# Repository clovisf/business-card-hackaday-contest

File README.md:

# business-card-hackaday-contest
 uC business card for Hackaday contest

 This is my try on an electronic business card for the 2024 Hackaday business card contest

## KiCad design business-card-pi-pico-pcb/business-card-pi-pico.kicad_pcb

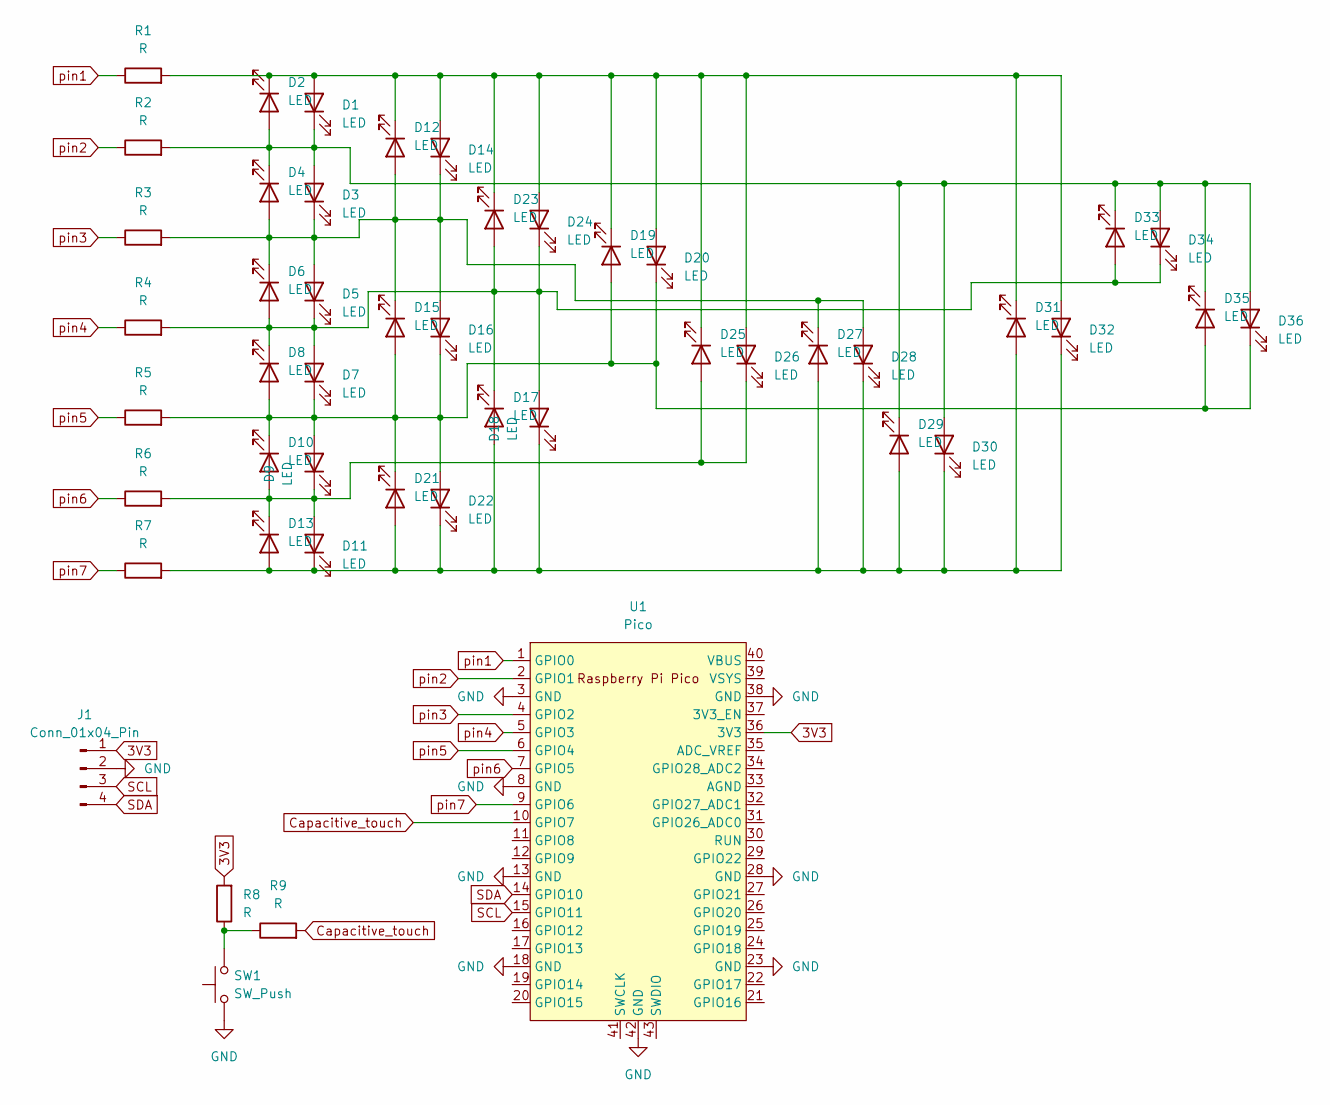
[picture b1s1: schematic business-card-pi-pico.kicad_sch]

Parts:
D1, D2, D3, D4, D5, D6, D7, D8, D9, D10, D11, D12, D13, D14, D15, D16, D17, D18, D19, D20, D21, D22, D23, D24, D25, D26, D27, D28, D29, D30, D31, D32, D33, D34, D35, D36: LED; LED_0805_2012Metric
J1: Conn_01x04_Pin; 128x64OLED
R1, R2, R3, R4, R5, R6, R7, R8, R9: R; R_0805_2012Metric
SW1: SW_Push; SW_PUSH_6mm_H8mm
U1: Pico; RPi_Pico_SMD_TH

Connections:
3V3: J1.1, R8.2, U1.36 (3V3)
Capacitive_touch: R9.2, U1.10 (GPIO7)
GND: J1.2, SW1.1, U1.3 (GND), U1.8 (GND), U1.13 (GND), U1.18 (GND), U1.23 (GND), U1.28 (GND), U1.38 (GND), U1.42 (GND)
unnamed: D1.2 (A), D2.1 (K), D12.1 (K), D14.2 (A), D19.1 (K), D20.2 (A), D23.1 (K), D24.2 (A), D25.1 (K), D26.2 (A), D31.1 (K), D32.2 (A), R1.2
unnamed: D1.1 (K), D2.2 (A), D3.2 (A), D4.1 (K), D29.1 (K), D30.2 (A), D33.1 (K), D34.2 (A), D35.1 (K), D36.2 (A), R2.2
unnamed: D9.1 (K), D10.2 (A), D11.2 (A), D13.1 (K), D25.2 (A), D26.1 (K), R6.2
unnamed: D7.1 (K), D8.2 (A), D9.2 (A), D10.1 (K), D15.2 (A), D16.1 (K), D19.2 (A), D20.1 (K), D21.1 (K), D22.2 (A), D35.2 (A), D36.1 (K), R5.2
unnamed: D11.1 (K), D13.2 (A), D17.2 (A), D18.1 (K), D21.2 (A), D22.1 (K), D27.2 (A), D28.1 (K), D29.2 (A), D30.1 (K), D31.2 (A), D32.1 (K), R7.2
unnamed: D3.1 (K), D4.2 (A), D5.2 (A), D6.1 (K), D12.2 (A), D14.1 (K), D15.1 (K), D16.2 (A), D27.1 (K), D28.2 (A), R3.2
unnamed: D5.1 (K), D6.2 (A), D7.2 (A), D8.1 (K), D17.1 (K), D18.2 (A), D23.2 (A), D24.1 (K), D33.2 (A), D34.1 (K), R4.2
unnamed: R8.1, R9.1, SW1.2
SCL: J1.3, U1.15 (GPIO11)
SDA: J1.4, U1.14 (GPIO10)
pin1: R1.1, U1.1 (GPIO0)
pin2: R2.1, U1.2 (GPIO1)
pin3: R3.1, U1.4 (GPIO2)
pin4: R4.1, U1.5 (GPIO3)
pin5: R5.1, U1.6 (GPIO4)
pin6: R6.1, U1.7 (GPIO5)
pin7: R7.1, U1.9 (GPIO6)

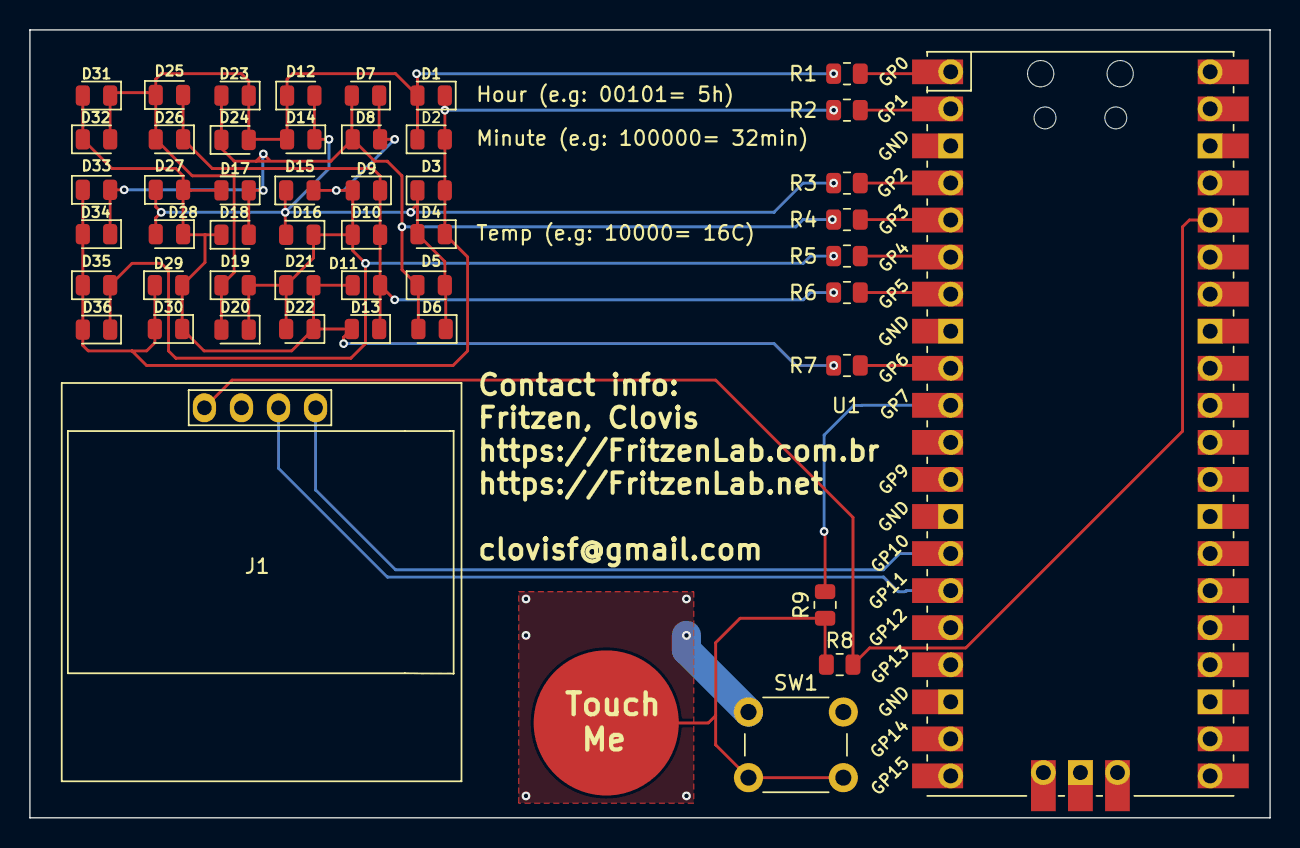
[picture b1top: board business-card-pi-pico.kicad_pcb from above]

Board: 2 copper layers, 85.0 x 54.0 mm, 48 parts (0 on the bottom side), 20 nets.

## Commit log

2024-05-09 first commit of PCB business card
    first commit of PCB business card
2024-05-09 updated readme
    updated readme with basic info about the project
2024-05-09 continued working on PCB
    continued working on PCB
2024-05-09 PCB updated a bit
    PCB updated a bit
2024-05-10 added SSD13006 display
    added SSD13006 display and push button
2024-05-10 Continue working on PCB
    Continue working on PCB, added button/touch input pin
2024-05-10 just a test
    just a test
2024-05-11 updated PCB
    updated PCB
2024-05-11 design finished
    design finished, sent PCB to fab at JLCPCB
2024-06-12 zip files
2024-06-14 backup files
2024-06-21 backups
2024-07-04 backup
